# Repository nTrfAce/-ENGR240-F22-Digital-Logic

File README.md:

# ENGR240-F22-Digital-Logic

APU Engineering and Computer Science has used the [Lattic Semiconductor iCEstick](https://www.digikey.com/en/products/detail/lattice-semiconductor-corporation/ICE40HX1K-STICK-EVN/4289604) as the FPGA development board for a few years in our [ENGR 240 Digital Logic](http://catalog.apu.edu/search/?search=ENGR+240) course, but this semester it is out of stock everywhere.

Students are creating carrier boards which will make use of the [Devantech iceWerx module](https://www.robotshop.com/en/devantech-icewerx-ice40-hx8k-fpga.html).  Each student will design a PCB which they will then solder, test, and use as their development board which they will use while learning Digital Logic, first with simple gate-level designs, then non-trivial systems using the Verilog Hardware Description Language (HDL).

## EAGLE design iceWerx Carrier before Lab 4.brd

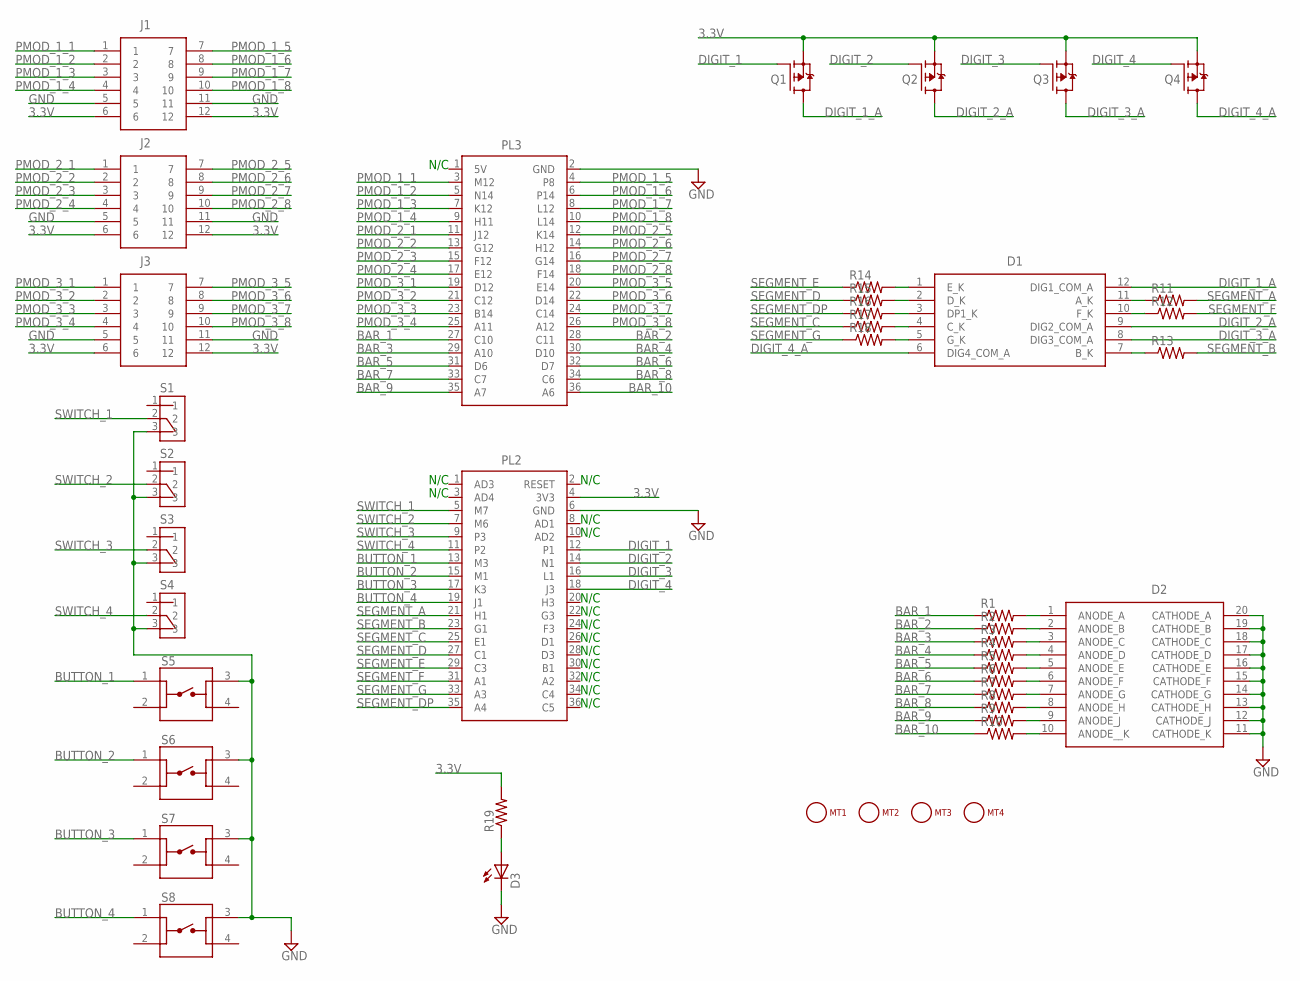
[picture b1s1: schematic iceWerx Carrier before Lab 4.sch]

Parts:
D1: LDQ-M282RI; LDQM282RI
D2: LTA-1000G; DIPS762W50P254L2527H825Q20N
D3: LED5MM
J1, J2, J3: PMOD-SOCKET-FOR-HOST-BOARD
MT1, MT2, MT3, MT4: MOUNTING_HOLE-125_250_ROUND; MT_125_250
PL2: ICEWERX-PL2; TE_4-1734506-1
PL3: ICEWERX-PL3; TE_4-1734506-1
Q1, Q2, Q3, Q4: NX2301P; SOT95P230X110-3N
R1, R2, R3, R4, R5, R6, R7, R8, R9, R10, R11, R12, R13, R14, R15, R16, R17, R18, R19: R-US_0204/5; 0204/5
S1, S2, S3, S4: OS102011MS2QN1; SW_OS102011MS2QN1
S5, S6, S7, S8: 1825910-7; SW_1825910-7

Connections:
3.3V: J1.6, J1.12, J2.6, J2.12, J3.6, J3.12, PL2.4 (3V3), Q1.2 (S), Q2.2 (S), Q3.2 (S), Q4.2 (S), R19.2
BAR_1: PL3.27 (C10), R1.1
BAR_2: PL3.28 (C11), R2.1
BAR_3: PL3.29 (A10), R3.1
BAR_4: PL3.30 (D10), R4.1
BAR_5: PL3.31 (D6), R5.1
BAR_6: PL3.32 (D7), R6.1
BAR_7: PL3.33 (C7), R7.1
BAR_8: PL3.34 (C6), R8.1
BAR_9: PL3.35 (A7), R9.1
BAR_10: PL3.36 (A6), R10.1
BUTTON_1: PL2.13 (M3), S5.1
BUTTON_2: PL2.15 (M1), S6.1
BUTTON_3: PL2.17 (K3), S7.1
BUTTON_4: PL2.19 (J1), S8.1
DIGIT_1: PL2.12 (P1), Q1.1 (G)
DIGIT_1_A: D1.12 (DIG1_COM_A), Q1.3 (D)
DIGIT_2: PL2.14 (N1), Q2.1 (G)
DIGIT_2_A: D1.9 (DIG2_COM_A), Q2.3 (D)
DIGIT_3: PL2.16 (L1), Q3.1 (G)
DIGIT_3_A: D1.8 (DIG3_COM_A), Q3.3 (D)
DIGIT_4: PL2.18 (J3), Q4.1 (G)
DIGIT_4_A: D1.6 (DIG4_COM_A), Q4.3 (D)
GND: D2.11 (CATHODE_K), D2.12 (CATHODE_J), D2.13 (CATHODE_H), D2.14 (CATHODE_G), D2.15 (CATHODE_F), D2.16 (CATHODE_E), D2.17 (CATHODE_D), D2.18 (CATHODE_C), D2.19 (CATHODE_B), D2.20 (CATHODE_A), D3.K (C), J1.5, J1.11, J2.5, J2.11, J3.5, J3.11, PL2.6 (GND), PL3.2 (GND), S1.3, S2.3, S3.3, S4.3, S5.3, S6.3, S7.3, S8.3
unnamed: D2.1 (ANODE_A), R1.2
unnamed: D2.2 (ANODE_B), R2.2
unnamed: D2.3 (ANODE_C), R3.2
unnamed: D2.4 (ANODE_D), R4.2
unnamed: D2.5 (ANODE_E), R5.2
unnamed: D2.6 (ANODE_F), R6.2
unnamed: D2.7 (ANODE_G), R7.2
unnamed: D2.8 (ANODE_H), R8.2
unnamed: D2.9 (ANODE_J), R9.2
unnamed: D2.10 (ANODE__K), R10.2
unnamed: D1.11 (A_K), R11.1
unnamed: D1.10 (F_K), R12.1
unnamed: D1.7 (B_K), R13.1
unnamed: D1.1 (E_K), R14.2
unnamed: D1.2 (D_K), R15.2
unnamed: D1.3 (DP1_K), R16.2
unnamed: D1.4 (C_K), R17.2
unnamed: D1.5 (G_K), R18.2
unnamed: D3.A, R19.1
PMOD_1_1: J1.1, PL3.3 (M12)
PMOD_1_2: J1.2, PL3.5 (N14)
PMOD_1_3: J1.3, PL3.7 (K12)
PMOD_1_4: J1.4, PL3.9 (H11)
PMOD_1_5: J1.7, PL3.4 (P8)
PMOD_1_6: J1.8, PL3.6 (P14)
PMOD_1_7: J1.9, PL3.8 (L12)
PMOD_1_8: J1.10, PL3.10 (L14)
PMOD_2_1: J2.1, PL3.11 (J12)
PMOD_2_2: J2.2, PL3.13 (G12)
PMOD_2_3: J2.3, PL3.15 (F12)
PMOD_2_4: J2.4, PL3.17 (E12)
PMOD_2_5: J2.7, PL3.12 (K14)
PMOD_2_6: J2.8, PL3.14 (H12)
PMOD_2_7: J2.9, PL3.16 (G14)
PMOD_2_8: J2.10, PL3.18 (F14)
PMOD_3_1: J3.1, PL3.19 (D12)
PMOD_3_2: J3.2, PL3.21 (C12)
PMOD_3_3: J3.3, PL3.23 (B14)
PMOD_3_4: J3.4, PL3.25 (A11)
PMOD_3_5: J3.7, PL3.20 (E14)
PMOD_3_6: J3.8, PL3.22 (D14)
PMOD_3_7: J3.9, PL3.24 (C14)
PMOD_3_8: J3.10, PL3.26 (A12)
SEGMENT_A: PL2.21 (H1), R11.2
SEGMENT_B: PL2.23 (G1), R13.2
SEGMENT_C: PL2.25 (E1), R17.1
SEGMENT_D: PL2.27 (C1), R15.1
SEGMENT_DP: PL2.35 (A4), R16.1
SEGMENT_E: PL2.29 (C3), R14.1
SEGMENT_F: PL2.31 (A1), R12.2
SEGMENT_G: PL2.33 (A3), R18.1
SWITCH_1: PL2.5 (M7), S1.2
SWITCH_2: PL2.7 (M6), S2.2
SWITCH_3: PL2.9 (P3), S3.2
SWITCH_4: PL2.11 (P2), S4.2

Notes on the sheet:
N/C

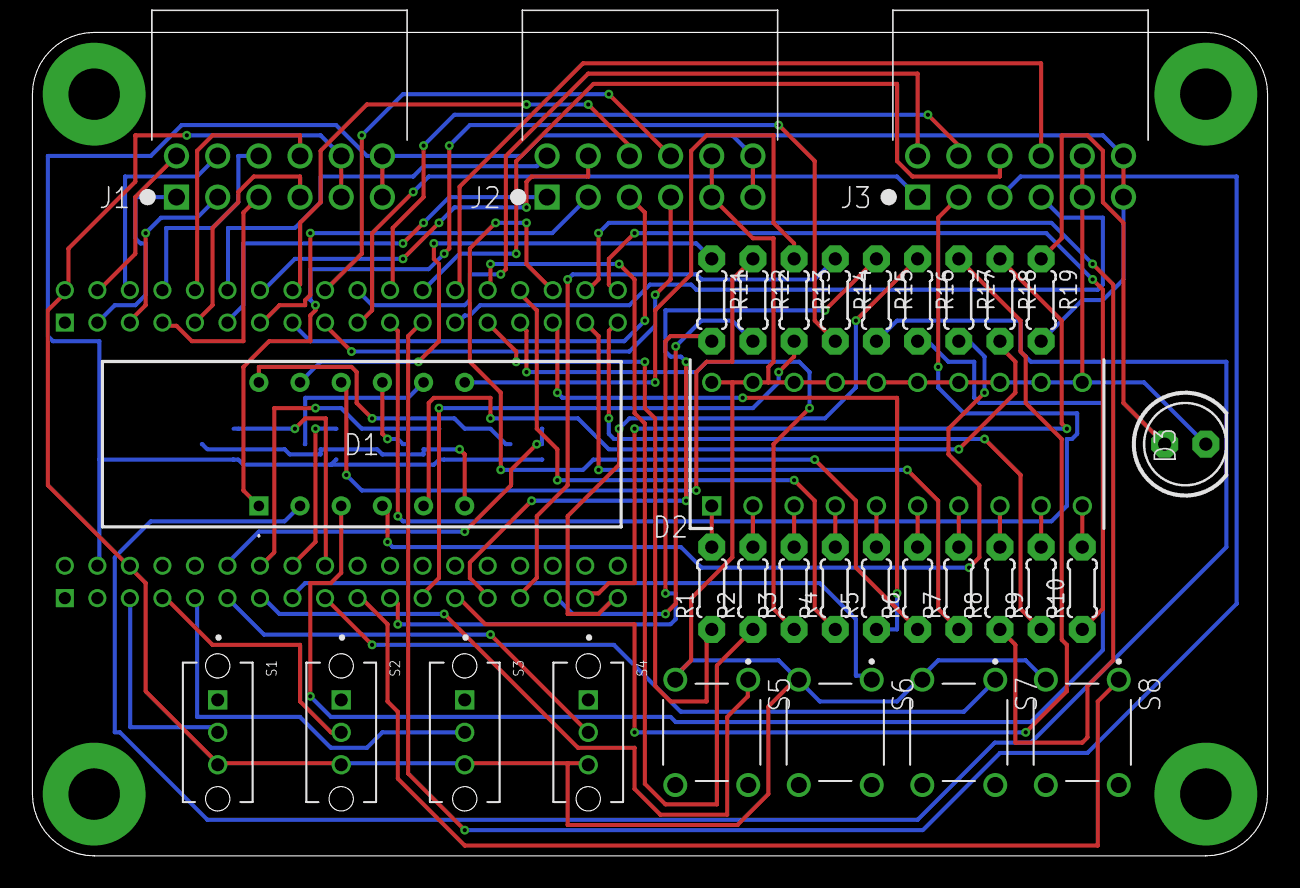
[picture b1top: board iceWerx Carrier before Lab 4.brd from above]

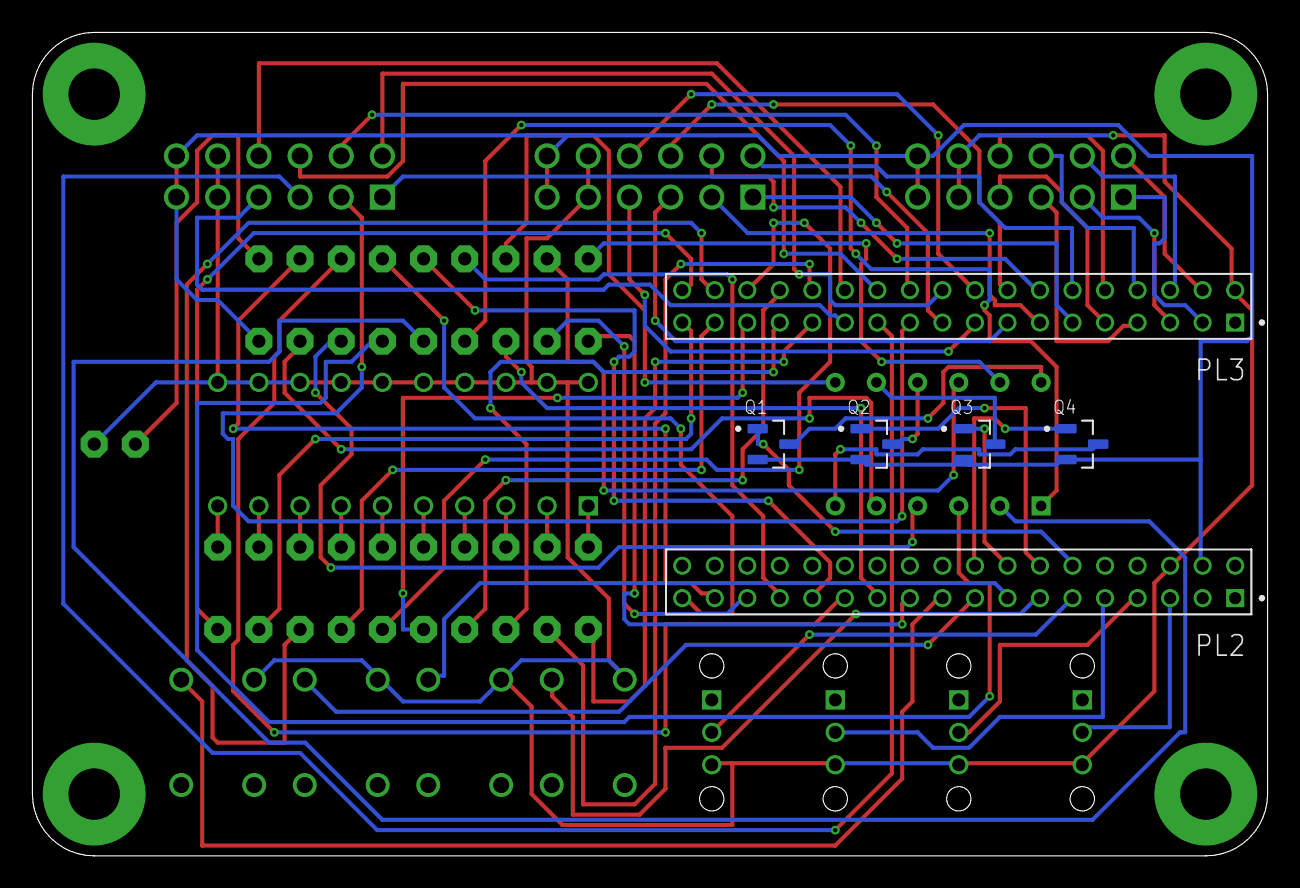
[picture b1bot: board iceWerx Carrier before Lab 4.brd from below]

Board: 2 copper layers, 76.2 x 50.8 mm, 43 parts (6 on the bottom side), 79 nets.

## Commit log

2022-09-22 add Eagle library
2022-09-22 Add Eagle design and PDFs
2022-09-22 Add rendered image of PCB
2022-09-22 add rendered PCB image
